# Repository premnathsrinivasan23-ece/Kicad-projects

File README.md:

# Kicad-projects
My KiCad projects and circuit simulations.

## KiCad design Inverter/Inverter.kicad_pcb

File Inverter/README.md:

# Inverter Circuit

KiCad files and circuit simulation for an inverter circuit.
⚡ Inverter Circuit Simulation
📌 Project Overview

This project demonstrates the design and simulation of an inverter circuit using KiCad. An inverter is an electronic circuit that converts a DC supply into an AC output.

The circuit uses switching components to periodically change the direction of current through the load, thereby producing an alternating output waveform.

🎯 Objective

The main objective of this project is:

To understand the working principle of an inverter.
To design the inverter circuit using KiCad.
To simulate the circuit and observe the input and output waveforms.
To study the conversion of DC power into AC power.
⚙️ Working Principle

The inverter receives a DC input voltage from a power source.

The switching circuit operates alternately, causing the output voltage to change polarity periodically. This creates an alternating waveform at the output.

In simple terms:

DC Input
   ↓
Switching Circuit
   ↓
Alternating Switching Action
   ↓
AC Output
🖼️ Circuit Design

The circuit schematic was designed using KiCad.

The schematic shows the different electronic components and their connections required for converting the DC input into an alternating output.

Circuit Diagram

Add your circuit image here.

📊 Simulation Results

The circuit was simulated to verify the operation of the inverter.

The simulation results show:

Input DC voltage.
Switching operation.
Output waveform.
Conversion of DC voltage into an alternating waveform.
Output Waveform

Add your simulation waveform image here.

🛠️ Tools Used
KiCad
KiCad Simulator
Electronic Circuit Components
🚀 Conclusion

This project successfully demonstrates the basic operation of an inverter circuit. The circuit converts DC electrical power into an alternating output using electronic switching.

The project helps in understanding power electronics, circuit design, switching operation, and circuit simulation using KiCad.

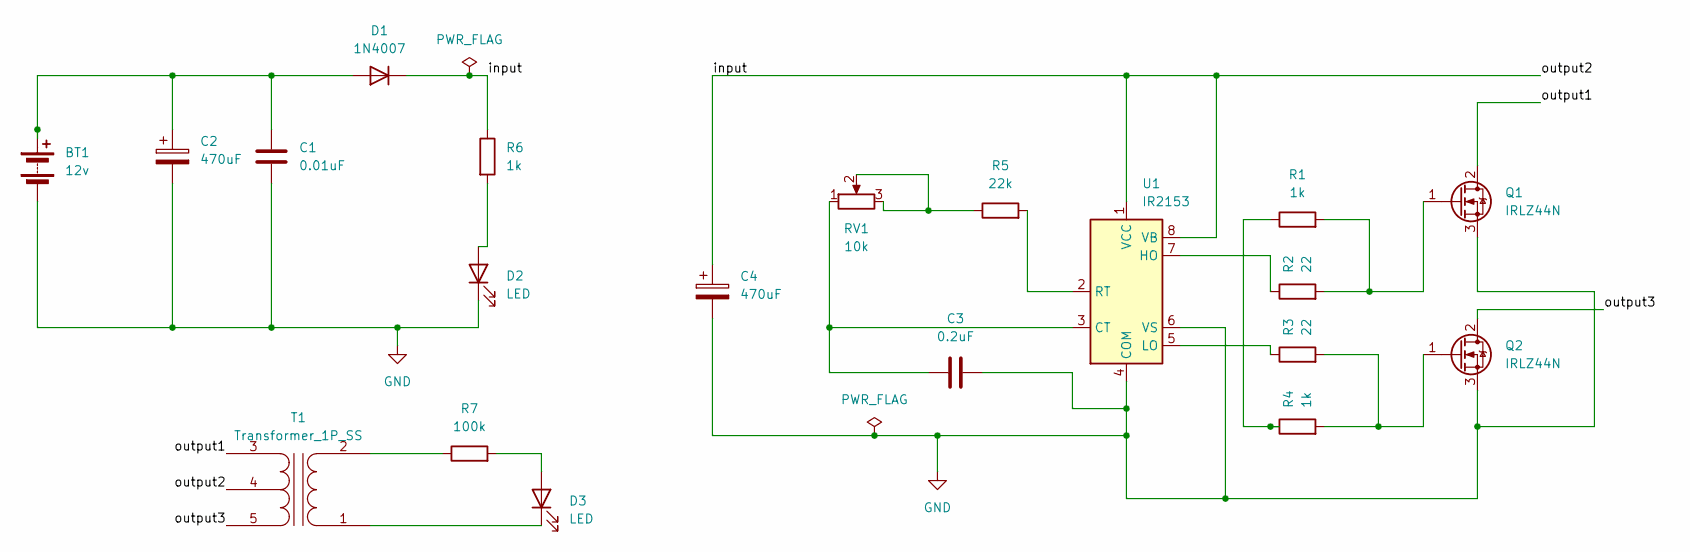
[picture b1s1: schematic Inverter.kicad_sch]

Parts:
BT1: 12v; TerminalBlock_Xinya_XY308-2.54-2P_1x02_P2.54mm_Horizontal
C1: 0.01uF; C_Disc_D5.0mm_W2.5mm_P5.00mm
C2, C4: 470uF; C_Radial_D8.0mm_H7.0mm_P3.50mm
C3: 0.2uF; C_Disc_D5.0mm_W2.5mm_P5.00mm
D1: 1N4007; D_DO-41_SOD81_P10.16mm_Horizontal
D2, D3: LED; LED_D5.0mm
Q1, Q2: IRLZ44N; TO-220-3_Vertical
R1, R4, R6: 1k; R_Axial_DIN0207_L6.3mm_D2.5mm_P10.16mm_Horizontal
R2, R3: 22; R_Axial_DIN0207_L6.3mm_D2.5mm_P10.16mm_Horizontal
R5: 22k; R_Axial_DIN0207_L6.3mm_D2.5mm_P10.16mm_Horizontal
R7: 100k; R_Axial_DIN0207_L6.3mm_D2.5mm_P10.16mm_Horizontal
RV1: 10k; Potentiometer_ACP_CA6-H2,5_Horizontal
T1: Transformer_1P_SS; TerminalBlock_Xinya_XY308-2.54-5P_1x05_P2.54mm_Horizontal
U1: IR2153; DIP-8_W7.62mm

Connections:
/input: C4.1, D1.1 (K), R6.1, T1.4 (SC), U1.1 (VCC), U1.8 (VB)
/output1: Q1.2 (D), T1.3 (SA)
/output3: Q2.2 (D), T1.5 (SB)
GND: BT1.2 (-), C1.2, C2.2, C3.2, C4.2, D2.1 (K), Q1.3 (S), Q2.3 (S), U1.4 (COM), U1.6 (VS)
unnamed: BT1.1 (+), C1.1, C2.1, D1.2 (A)
unnamed: D2.2 (A), R6.2
unnamed: D3.2 (A), R7.2
unnamed: D3.1 (K), T1.1 (AA)
unnamed: Q1.1 (G), R1.2, R2.2
unnamed: Q2.1 (G), R3.2, R4.2
unnamed: R1.1, R4.1
unnamed: R5.1, RV1.2, RV1.3
unnamed: R7.1, T1.2 (AB)
unnamed: C3.1, RV1.1, U1.3 (CT)
unnamed: R2.1, U1.7 (HO)
unnamed: R3.1, U1.5 (LO)
unnamed: R5.2, U1.2 (RT)

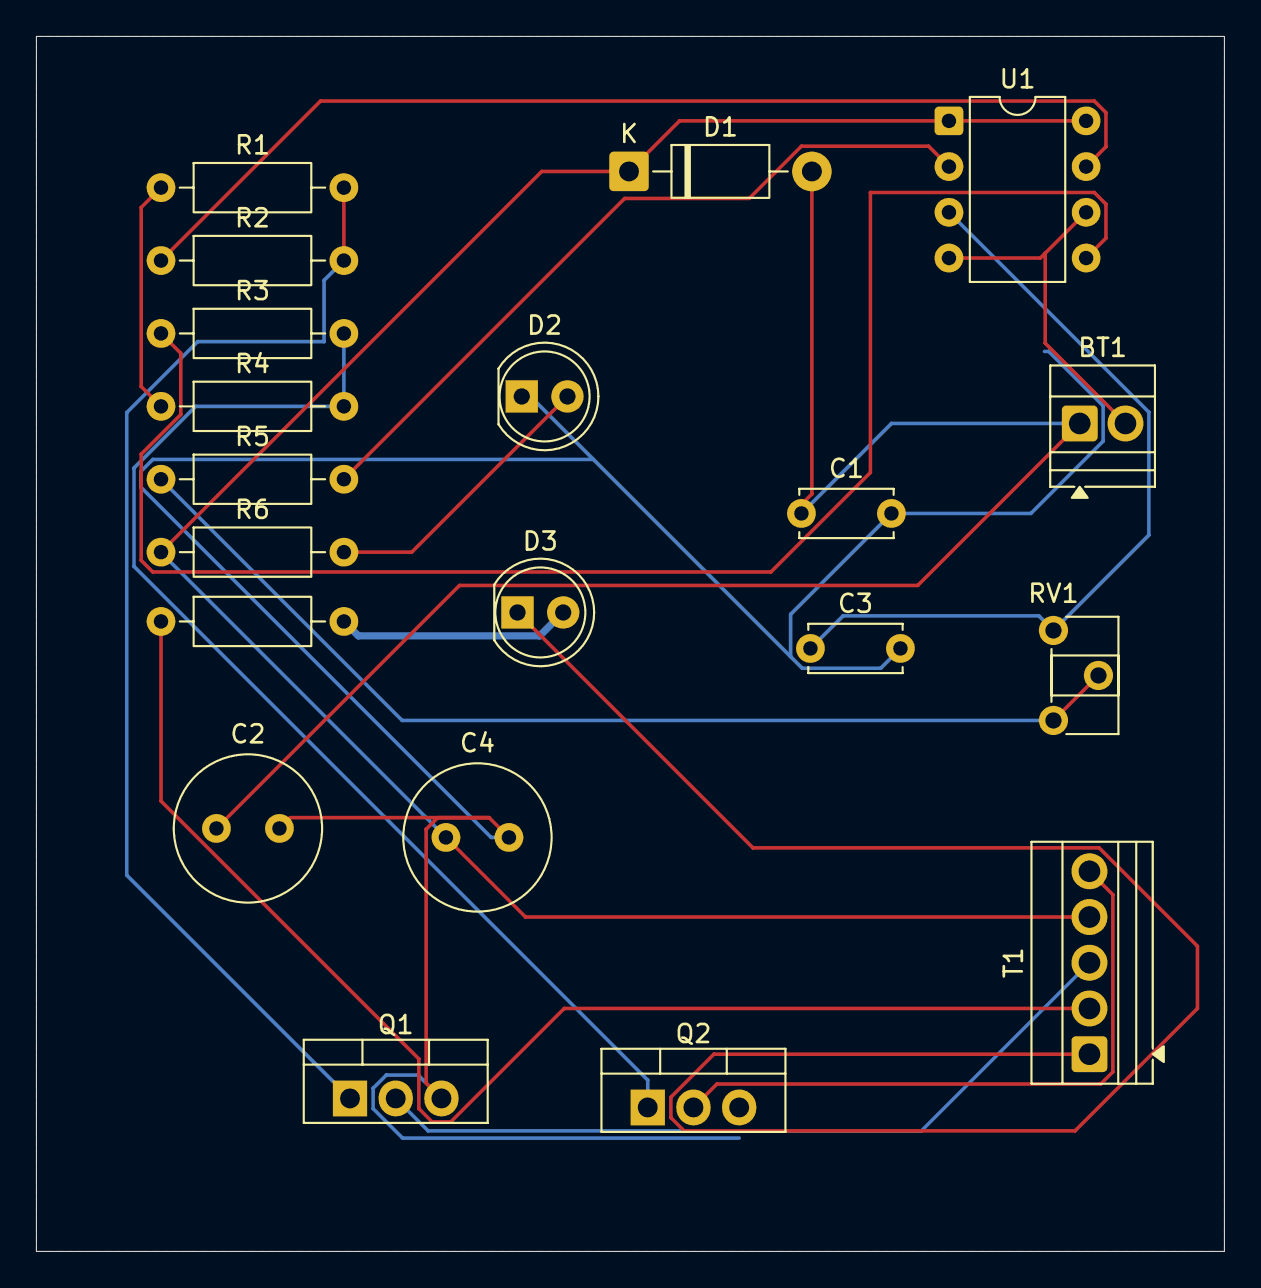
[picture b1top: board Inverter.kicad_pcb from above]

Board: 2 copper layers, 66.0 x 67.5 mm, 20 parts (0 on the bottom side), 17 nets.
